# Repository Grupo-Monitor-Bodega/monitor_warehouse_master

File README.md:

# Sistemas Embebidos
# Monitor Warehouse

* Diego Chaparro

* Juan Diego Carrero

* Raúl Morales

Repositorio del proyecto de la asignatura "Sistemas Embebidos" de la Universidad Nacional de Colombia, sede Bogotá. Aquí encontrará el proyecto del monitor de bodega, con toda la documentación requerida y el diseño completo del mismo.

El proyecto consiste en un monitor que tomará los datos relacionados a la temperatura y humedad en una bodega, en la cual se almacenan granos de café. Para el correcto almacenamiento del café es necesario monitorear los niveles de humedad a los que este se encuentra expuesto, la cual a su vez tiene relación con la temperatura; con base a estos requerimientos, el café requiere que la humedad se encuentre establecida en un rango entre 10.3 y 11.3%, esta a su vez es afectada por las condiciones medioambientales a la que la bodega se encuentra expuesta. El tiempo que duran los bultos de café dentro de la bodega varía dependiendo del tipo, siendo este tiempo de algunos día e incluso puede alcanzar los 10 meses de almacenamiento, en los que se realizan ciertas rotaciones dentro de la bodega.

Se busca que el dispositivo final sea lo más pequeño posible con el fin de facilitar su portabilidad, por otra parte, se requiere que exista la posibilidad de realizar un monitoreo de forma remota y como requerimiento opcional, de realizar a su vez un historial sobre las dos variables a lo largo del tiempo para futuras mejoras en cuanto a la operación de la bodega.

Para la ejecución del proyecto, se realizará primeramente un prototipo funcional haciendo uso de un microcontrolador ESP32, de un sensor Shtc3 de humedad y temperatura, una pantalla lcd, así como de una protoboard y cables necesarios. Una vez el prototipo sea funcional, se realizarán los diseños para la PCB y la caja necesaria para la contención del producto y fácil accesibilidad para el cliente.

Con el fin de realizar alguna revisión posterior al hardware y software, se disponen de dos pines para propósito general.

Por último, en la sección de "Wiki", se amplía la información relacionada con el proyecto.

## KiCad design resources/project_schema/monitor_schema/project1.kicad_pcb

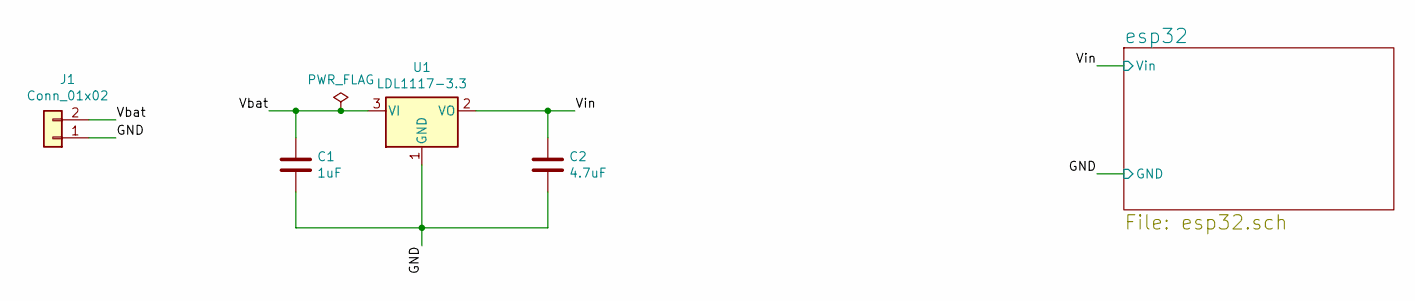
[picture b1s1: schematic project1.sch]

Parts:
C1: 1uF; C_0805_2012Metric_Pad1.18x1.45mm_HandSolder
C2: 4.7uF; C_0805_2012Metric_Pad1.18x1.45mm_HandSolder
J1: Conn_01x02; PinHeader_1x02_P2.54mm_Vertical
U1: LDL1117-3.3; SOT-223-3_TabPin2

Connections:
/GND: C1.2, C2.2, J1.1, U1.1 (GND); also elsewhere on the board
/Vbat: C1.1, J1.2, U1.3 (VI)
/Vin: C2.1, U1.2 (VO); also elsewhere on the board

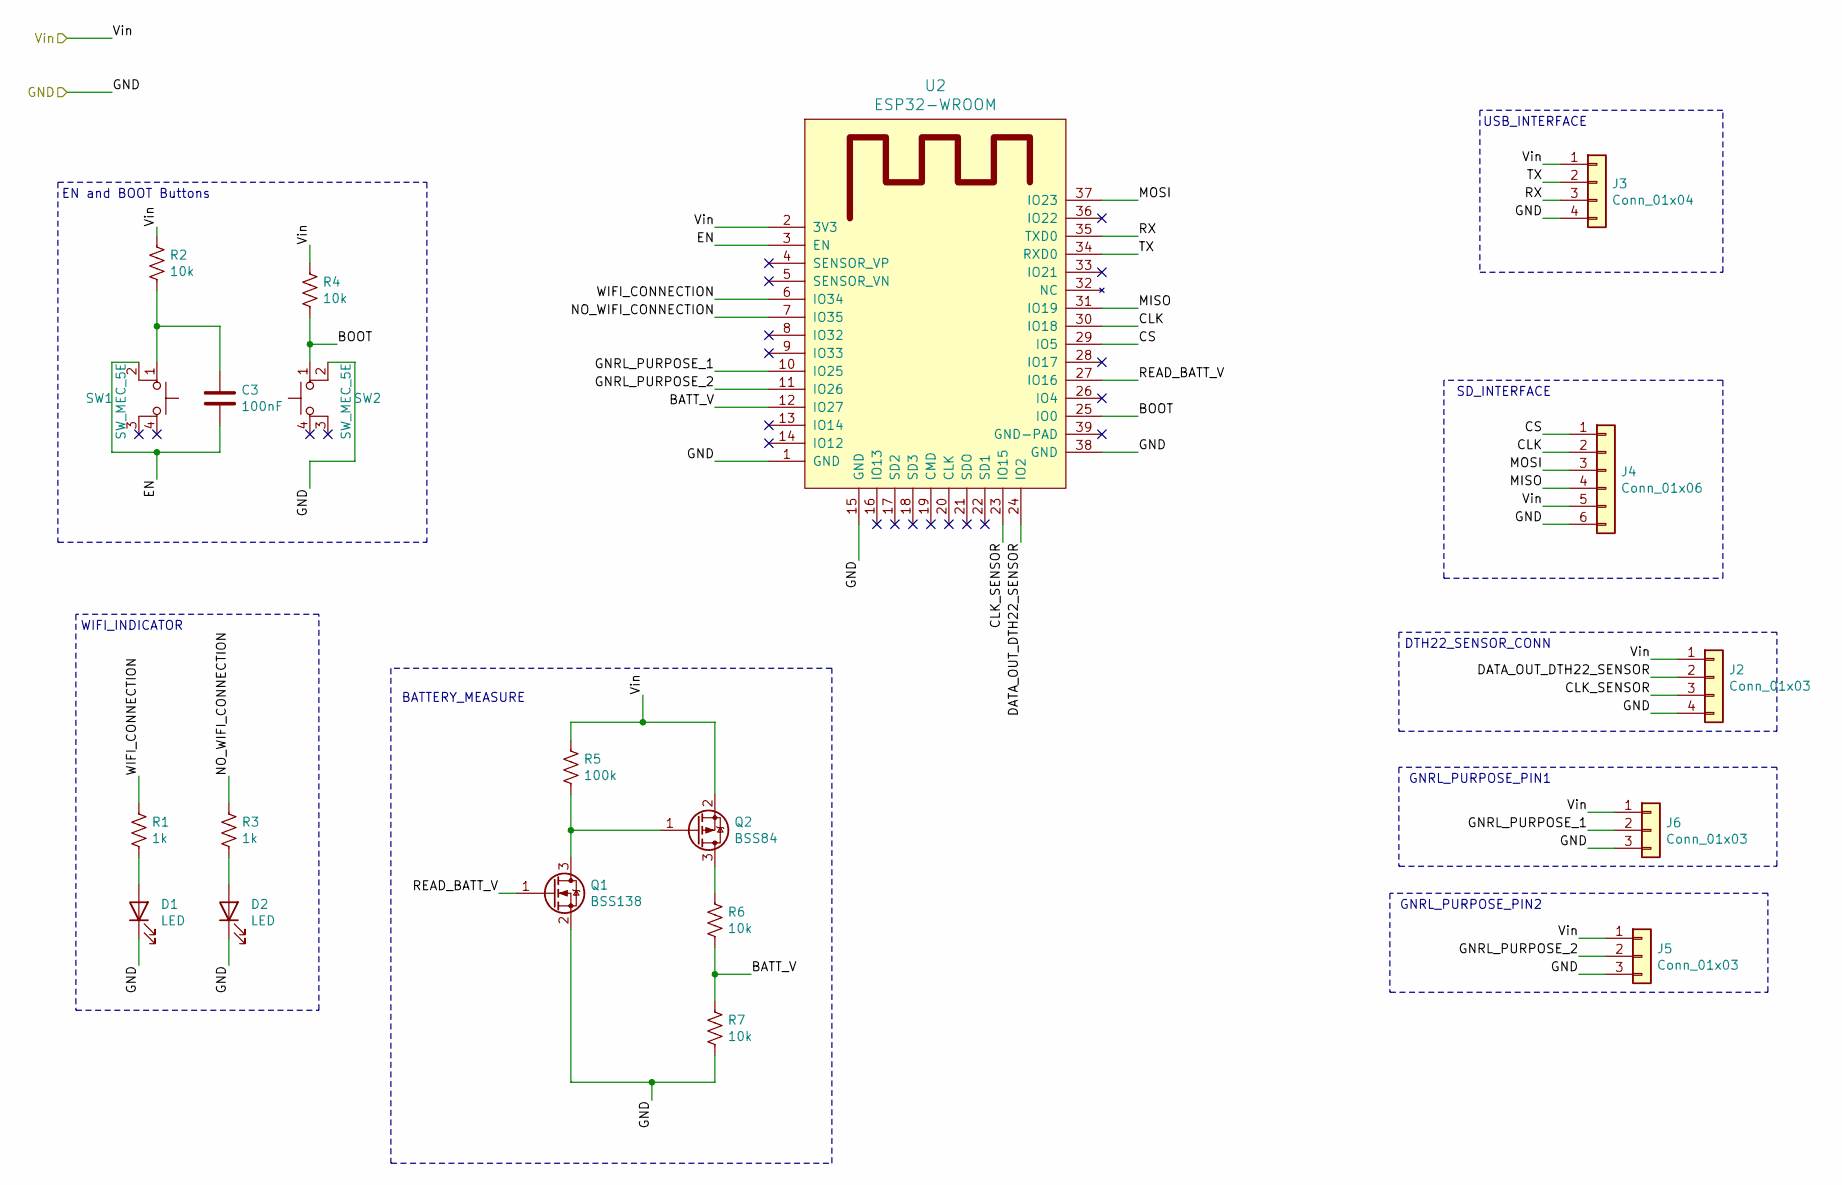
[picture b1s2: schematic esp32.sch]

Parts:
C3: 100nF; C_0805_2012Metric_Pad1.18x1.45mm_HandSolder
D1, D2: LED; LED_0805_2012Metric_Pad1.15x1.40mm_HandSolder
J2: Conn_01x03; PinHeader_1x04_P2.54mm_Vertical
J3: Conn_01x04; PinHeader_1x04_P2.54mm_Vertical
J4: Conn_01x06; PinHeader_1x06_P2.54mm_Vertical
J5, J6: Conn_01x03; PinHeader_1x03_P2.54mm_Vertical
Q1: BSS138; SOT-23
Q2: BSS84; SOT-23
R1, R3: 1k; R_0805_2012Metric_Pad1.20x1.40mm_HandSolder
R2, R4, R6, R7: 10k; R_0805_2012Metric_Pad1.20x1.40mm_HandSolder
R5: 100k; R_0805_2012Metric_Pad1.20x1.40mm_HandSolder
SW1, SW2: SW_MEC_5E; SW_Push_1P1T_NO_6x6mm_H9.5mm
U2: ESP32-WROOM; ESP32-WROOM-32E

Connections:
/GND: D1.1 (K), D2.1 (K), J2.4, J3.4, J4.6, J5.3, J6.3, Q1.2 (S), R7.2, SW2.2, U2.1 (GND), U2.15 (GND), U2.38 (GND); also elsewhere on the board
/Vin: J2.1, J3.1, J4.5, J5.1, J6.1, Q2.2 (S), R2.1, R4.1, R5.1, U2.2 (3V3); also elsewhere on the board
/esp32/BATT_V: R6.2, R7.1, U2.12 (IO27)
/esp32/BOOT: R4.2, SW2.1, U2.25 (IO0)
/esp32/CLK: J4.2, U2.30 (IO18)
/esp32/CLK_SENSOR: J2.3, U2.23 (IO15)
/esp32/CS: J4.1, U2.29 (IO5)
/esp32/DATA_OUT_DTH22_SENSOR: J2.2, U2.24 (IO2)
/esp32/EN: C3.1, SW1.2, U2.3 (EN)
/esp32/GNRL_PURPOSE_1: J6.2, U2.10 (IO25)
/esp32/GNRL_PURPOSE_2: J5.2, U2.11 (IO26)
/esp32/MISO: J4.4, U2.31 (IO19)
/esp32/MOSI: J4.3, U2.37 (IO23)
/esp32/NO_WIFI_CONNECTION: R3.1, U2.7 (IO35)
/esp32/RX: J3.3, U2.35 (TXD0)
/esp32/TX: J3.2, U2.34 (RXD0)
/esp32/WIFI_CONNECTION: R1.1, U2.6 (IO34)
unnamed: C3.2, R2.2, SW1.1
unnamed: D1.2 (A), R1.2
unnamed: D2.2 (A), R3.2
unnamed: Q1.3 (D), Q2.1 (G), R5.2
unnamed: Q2.3 (D), R6.1

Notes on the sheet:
WIFI_INDICATOR
DTH22_SENSOR_CONN
SD_INTERFACE
USB_INTERFACE
BATTERY_MEASURE
GNRL_PURPOSE_PIN1
GNRL_PURPOSE_PIN2
EN and BOOT Buttons

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
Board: 2 copper layers, 24 parts (0 on the bottom side), 24 nets, no tracks yet.

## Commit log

2021-10-25 Add directory with resources for project documentation
2021-11-02 Add block diagram file and image
2021-11-02 Create Datasheet Sensor SHTC3
2021-11-02 Create Datasheet Display Oled 0.91" I2C 128*32 SSD1306
2021-11-02 Create Protocol SSD1306
2021-11-04 Add related project links file
2022-01-11 add esp32 schema kicad
2022-01-16 add pwr batt sensor and pwr regulator
2022-01-18 Update pcb layout
2022-01-19 Pequeña modificación del esquematico
2022-01-19 Adelanto de PCB
2022-01-19 Modificación PCB por dos caras
2022-01-24 PCB layout
2022-01-25 PCB corregida con ancho de vias, corte y sujeción
2022-01-27 Change pnp transistor footprint
2022-01-27 Creación del comprimido grb para cotizar
2022-01-27 PCB images and some changes from schematic
2022-02-06 Add code for programming esp32
2022-02-07 SHTC3 server test
2022-02-08 test_sensor
2022-02-08 test_server_conn
2022-02-09 add micropython code
